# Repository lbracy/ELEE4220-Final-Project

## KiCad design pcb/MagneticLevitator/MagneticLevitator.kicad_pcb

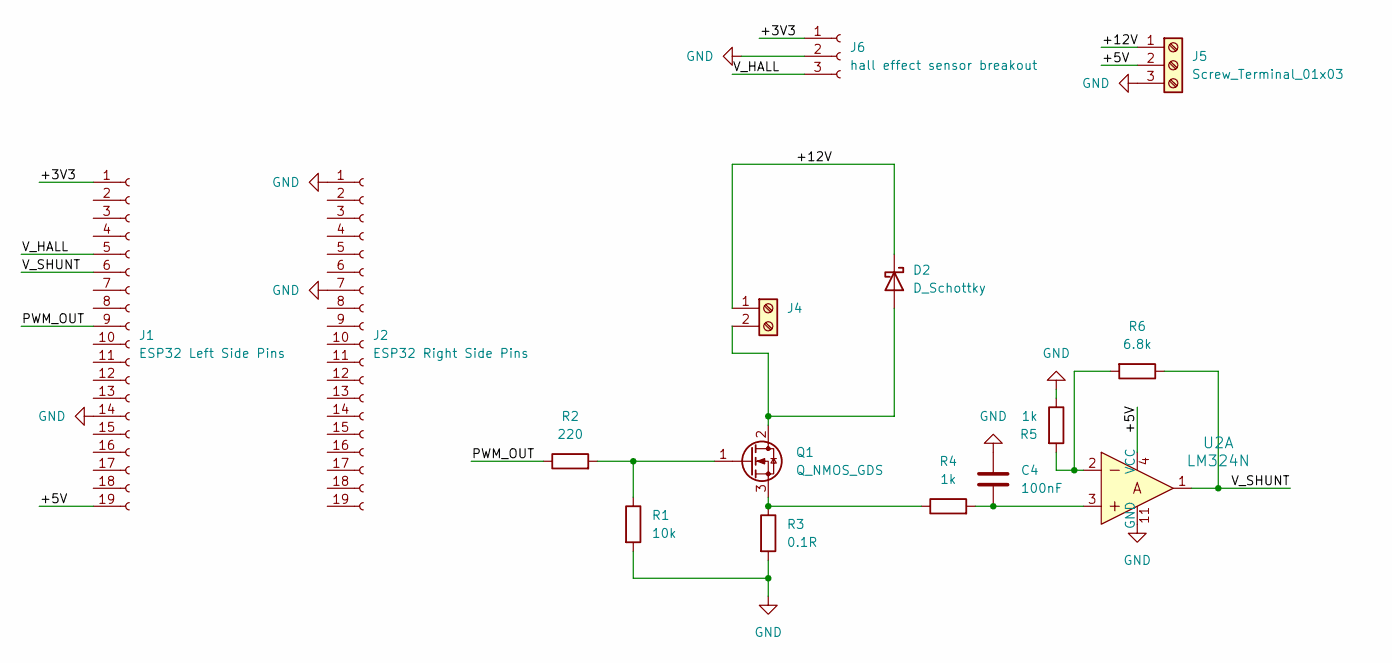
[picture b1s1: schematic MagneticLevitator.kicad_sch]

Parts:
C4: 100nF; C_Disc_D3.0mm_W1.6mm_P2.50mm
D2: D_Schottky; D_DO-201AD_P15.24mm_Horizontal
J1: ESP32 Left Side Pins; PinSocket_1x19_P2.54mm_Vertical
J2: ESP32 Right Side Pins; PinSocket_1x19_P2.54mm_Vertical
J4: Screw_Terminal_01x02; TerminalBlock_MaiXu_MX126-5.0-02P_1x02_P5.00mm
J5: Screw_Terminal_01x03; TerminalBlock_MaiXu_MX126-5.0-03P_1x03_P5.00mm
J6: hall effect sensor breakout; PinSocket_1x03_P2.54mm_Vertical
Q1: Q_NMOS_GDS; TO-220-3_Vertical
R1: 10k; R_Axial_DIN0207_L6.3mm_D2.5mm_P10.16mm_Horizontal
R2: 220; R_Axial_DIN0207_L6.3mm_D2.5mm_P10.16mm_Horizontal
R3: 0.1R; R_Axial_Power_L25.0mm_W9.0mm_P27.94mm
R4, R5: 1k; R_Axial_DIN0207_L6.3mm_D2.5mm_P10.16mm_Horizontal
R6: 6.8k; R_Axial_DIN0207_L6.3mm_D2.5mm_P10.16mm_Horizontal
U2: LM324N; DIP-14_W7.62mm; MPN LM324N; Digi-Key_PN 296-1391-5-ND

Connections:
/+3V3: J1.1, J6.1
/+5V: J1.19, J5.2, U2.4 (VCC)
/+12V: D2.1 (K), J4.1, J5.1
/PWM_OUT: J1.9, R2.1
/V_HALL: J1.5, J6.3
/V_SHUNT: J1.6, R6.1, U2.1
GND: C4.1, J1.14, J2.1, J2.7, J5.3, J6.2, R1.2, R3.2, R5.1, U2.11 (GND)
unnamed: C4.2, R4.2, U2.3
unnamed: D2.2 (A), J4.2, Q1.2 (D)
unnamed: Q1.1 (G), R1.1, R2.2
unnamed: Q1.3 (S), R3.1, R4.1
unnamed: R5.2, R6.2, U2.2

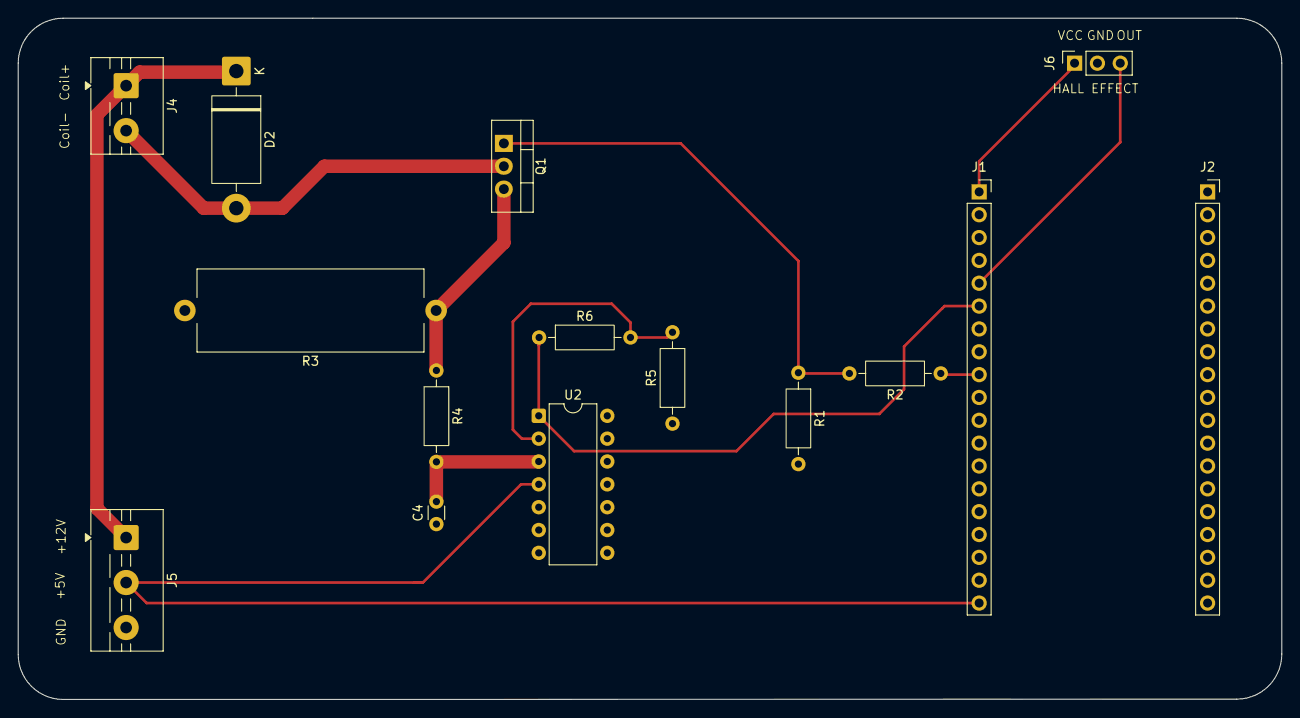
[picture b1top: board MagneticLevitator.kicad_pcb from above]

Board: 2 copper layers, 140.5 x 75.8 mm, 15 parts (0 on the bottom side), 12 nets.

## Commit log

2026-02-26 matlab doc
2026-03-03 pcb and doc started
2026-03-15 working on mathematical description
2026-03-15 pausing, must continue to definine the force felt by the magnet
2026-03-15 added background and lit study paragraph
2026-03-15 first iteration of model created
2026-03-16 plots of system added
2026-03-16 Finished math description, edited other deliverables, did Ails deliverable, added sources. need to clean up and submit
2026-03-16 cited source for wiki article abt maglev history
2026-03-17 labeled all figures and added sims back in
2026-03-22 updates to pcb
2026-03-22 more pcb updates
2026-03-25 added sensor and actuator sections to report
2026-03-27 something is wrong w the model in the block that models the Magnet and Mechanics...
2026-03-29 cooked
2026-03-30 chore: remove simulink cache and build files from tracking
2026-03-30 hardware
2026-03-30 fixed dummy gain stuff
2026-04-06 working on PI and PID tuning
2026-04-07 added pid and pi controller section
2026-04-09 code for mos
2026-04-10 working on checkpt 3
2026-04-10 ckpt 3 almost done, pid and pi tuning
2026-04-12 basic feedback
2026-04-12 current sensor works
2026-04-12 not great
2026-04-12 bruh
2026-04-13 moved to teensy
2026-04-13 PID tuning
2026-04-14 ughgggg alittle closer
2026-04-14 bruh again
2026-04-21 claude please help us
2026-04-21 inner loop is perfect
2026-04-23 tuningggggg
2026-04-26 still tuning :)
2026-04-26 keep on keeping on
2026-04-27 pain
